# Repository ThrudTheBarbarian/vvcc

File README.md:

# vvcc
Variable-VCC circuit using an RP2040

This is a test-board to try out using a variable-pot controlled by an RP2040 to 
in turn control the voltage of a voltage regulator. That voltage will then be
provided to the other side of a level-shifter to insulate an FPGA from different
voltage inputs.

The level shifter in question can run at >400 MHz, which is the max toggle frequency of
the FPGA.

Simultaneously, I wanted to test out the USB component of the RP2040 and make sure I had
the design correct before laying down the FPGA board (which is a lot more expensive). the
RP2040 will be the last bastion against a bricked FPGA, so it'd be good to know that 
worked too.

So basically a testing-ground. Enjoy.

Thrud

# Update 25/May/2022

Boards came back today, with slightly mixed results. Plugging the first board in, the leds flickered, presumably magic smoke exited stage left, and the 3.3v power rail was churning out 1.1v...

Checking everything against the schematic, it seemed ok, nothing was placed the wrong way around, and even running through the boot process and (re)checking the default value for the I2C-controlled resistance looked like the resulting voltage from IC5 would be ok (4.3v by default).

I was left wondering whether the boot process did weird things with GPIOs, which seems vanishingly unlikely, but ... Anyway, holding down reset & boot buttons on a second board made that boot up ok, appear as RPI2_BOOT on the Mac, and none of the LEDs flashed, 3.3v rail seems ok (LED lights) etc. 

So my advice is that if you get these made, make sure you initialise it with known firmware before letting it boot on its own. 

Note: There is a pullup missing on the /CS line for the flash, but it's also missing in the RP2040 hardware design guide with the comment that they found they didn't need it. I'll definitely include it in future mind.

If booting it with working firmware still results in a problem, I'll update this. It's also possible the first board was just a dud... Once I have tested out the firmware thing, I might try sacrificing another board to see if it has the same behaviour as the first when booted up with no firmware in place.

Thrud

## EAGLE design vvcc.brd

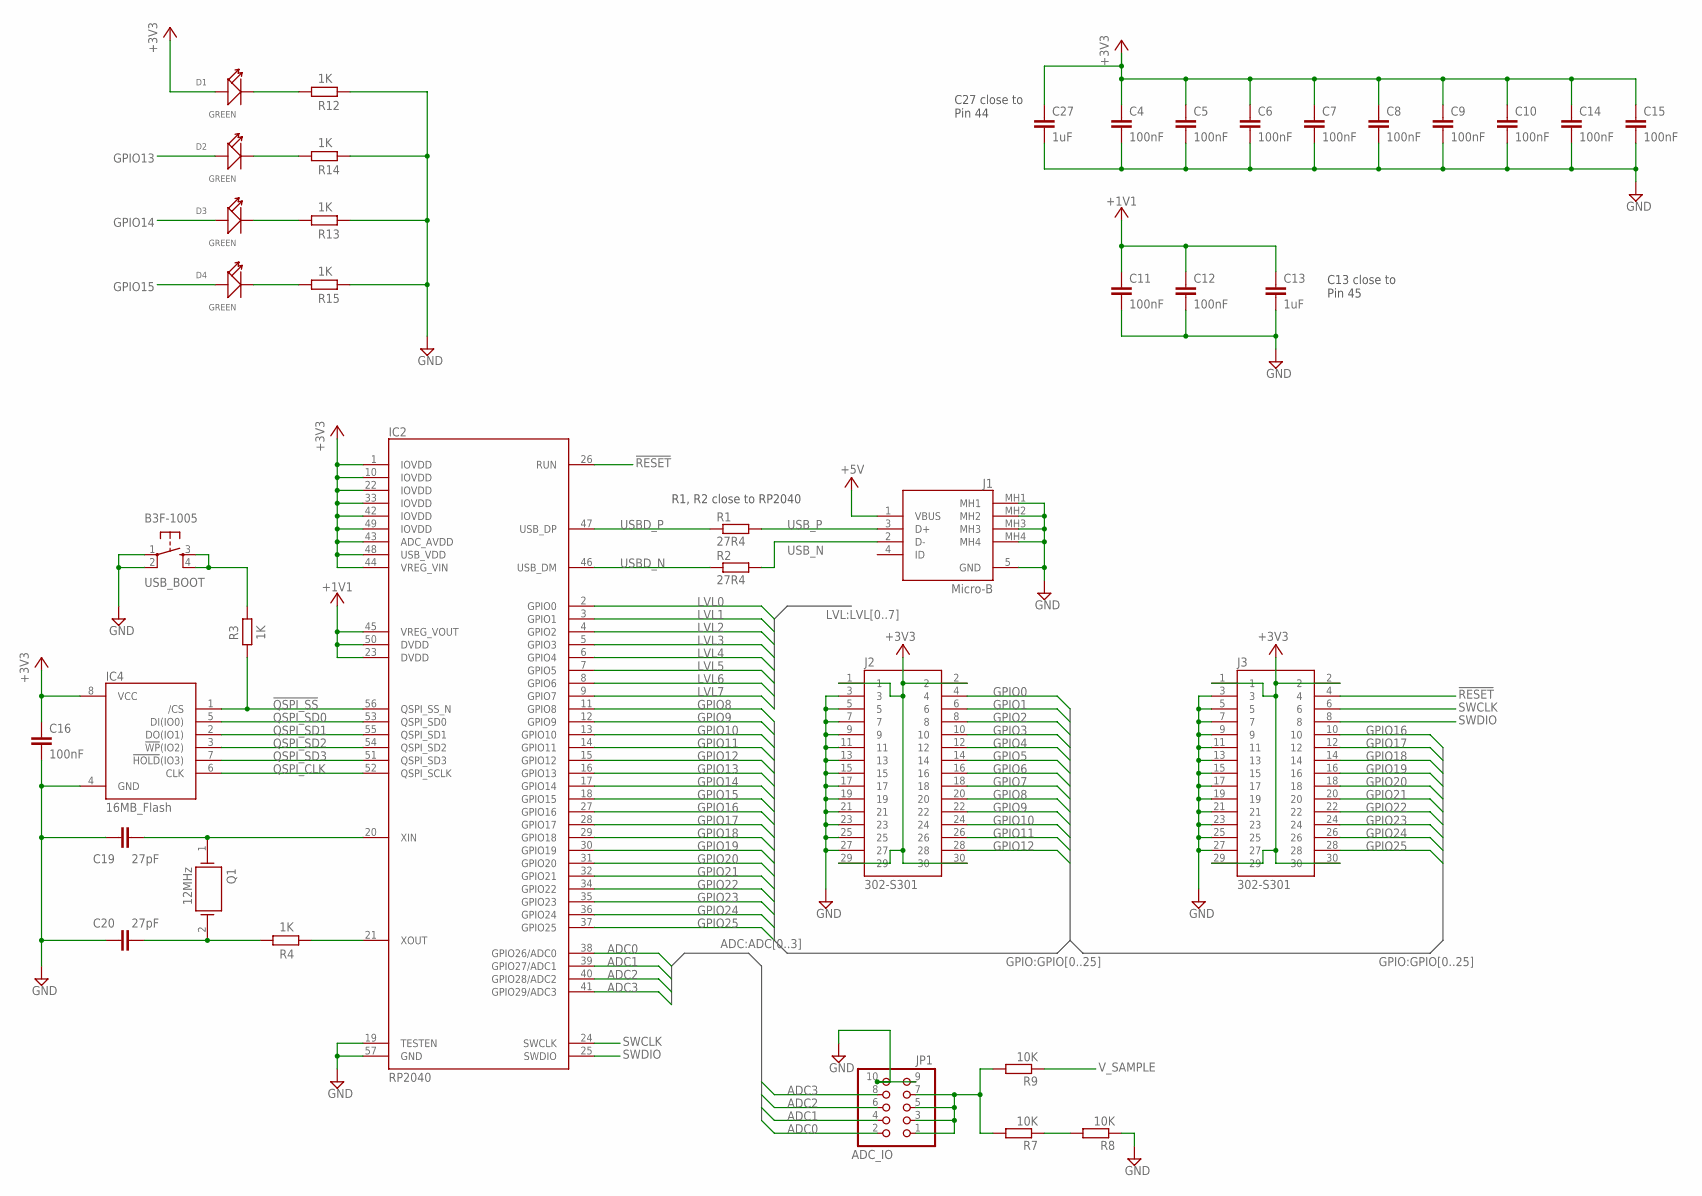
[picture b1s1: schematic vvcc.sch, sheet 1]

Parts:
C4, C5, C6, C7, C8, C9, C10, C11, C12, C14, C15, C16: 100nF; C0201
C13, C27: 1uF; C0201
C19, C20: 27pF; C0201
D1, D2, D3, D4: GREEN; LED-0603
IC2: RP2040; QFN40P700X700X90-57N
IC4: 16MB_Flash; SOIC127P790X216-8N
J1: Micro-B; MCRBSRASMTCS14TR
J2, J3: 302-S301; SHDR30W66P254_2X15_4572X910X91
JP1: ADC_IO; 2X05
Q1: 12MHz; HC/49US-(AT49)_1
R1, R2: 27R4; R0201
R3, R4, R12, R13, R14, R15: 1K; R0201
R7, R8, R9: 10K; R0201
USB_BOOT: B3F-1005; TACTILE-PTH

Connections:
!QSPI_SS!: IC2.56 (QSPI_SS_N), IC4.1 (/CS), R3.2
!RESET!: IC2.26 (RUN), J3.4; also elsewhere on the board
+1.8_FT: C11.1, C12.1, C13.1, IC2.23 (DVDD), IC2.45 (VREG_VOUT), IC2.50 (DVDD)
+3V3: C4.1, C5.1, C6.1, C7.1, C8.1, C9.1, C10.1, C14.1, C15.1, C16.1, C27.1, D1.+, IC2.1 (IOVDD), IC2.10 (IOVDD), IC2.22 (IOVDD), IC2.33 (IOVDD), IC2.42 (IOVDD), IC2.43 (ADC_AVDD), IC2.44 (VREG_VIN), IC2.48 (USB_VDD), IC2.49 (IOVDD), IC4.8 (VCC), J2.1, J2.2, J2.29, J2.30, J3.1, J3.2, J3.29, J3.30; also elsewhere on the board
+5V: J1.1 (VBUS); also elsewhere on the board
ADC0: IC2.38 (GPIO26/ADC0), JP1.2
ADC1: IC2.39 (GPIO27/ADC1), JP1.4
ADC2: IC2.40 (GPIO28/ADC2), JP1.6
ADC3: IC2.41 (GPIO29/ADC3), JP1.8
GND: C4.2, C5.2, C6.2, C7.2, C8.2, C9.2, C10.2, C11.2, C12.2, C13.2, C14.2, C15.2, C16.2, C19.2, C20.1, C27.2, IC2.19 (TESTEN), IC2.57 (GND), IC4.4 (GND), J1.5 (GND), J1.MH1, J1.MH2, J1.MH3, J1.MH4, J2.3, J2.5, J2.7, J2.9, J2.11, J2.13, J2.15, J2.17, J2.19, J2.21, J2.23, J2.25, J2.27, J3.3, J3.5, J3.7, J3.9, J3.11, J3.13, J3.15, J3.17, J3.19, J3.21, J3.23, J3.25, J3.27, JP1.9, JP1.10, R8.1, R12.2, R13.2, R14.2, R15.2, USB_BOOT.1, USB_BOOT.2; also elsewhere on the board
GPIO0: J2.4; also elsewhere on the board
GPIO1: J2.6; also elsewhere on the board
GPIO2: J2.8; also elsewhere on the board
GPIO3: J2.10; also elsewhere on the board
GPIO4: J2.12; also elsewhere on the board
GPIO5: J2.14; also elsewhere on the board
GPIO6: J2.16; also elsewhere on the board
GPIO7: J2.18; also elsewhere on the board
GPIO8: IC2.11 (GPIO8), J2.20; also elsewhere on the board
GPIO9: IC2.12 (GPIO9), J2.22; also elsewhere on the board
GPIO10: IC2.13 (GPIO10), J2.24
GPIO11: IC2.14 (GPIO11), J2.26
GPIO12: IC2.15 (GPIO12), J2.28; also elsewhere on the board
GPIO13: D2.+, IC2.16 (GPIO13); also elsewhere on the board
GPIO14: D3.+, IC2.17 (GPIO14)
GPIO15: D4.+, IC2.18 (GPIO15)
GPIO16: IC2.27 (GPIO16), J3.10
GPIO17: IC2.28 (GPIO17), J3.12
GPIO18: IC2.29 (GPIO18), J3.14
GPIO19: IC2.30 (GPIO19), J3.16
GPIO20: IC2.31 (GPIO20), J3.18
GPIO21: IC2.32 (GPIO21), J3.20
GPIO22: IC2.34 (GPIO22), J3.22
GPIO23: IC2.35 (GPIO23), J3.24
GPIO24: IC2.36 (GPIO24), J3.26
GPIO25: IC2.37 (GPIO25), J3.28
LVL0: IC2.2 (GPIO0); also elsewhere on the board
LVL1: IC2.3 (GPIO1); also elsewhere on the board
LVL2: IC2.4 (GPIO2); also elsewhere on the board
LVL3: IC2.5 (GPIO3); also elsewhere on the board
LVL4: IC2.6 (GPIO4); also elsewhere on the board
LVL5: IC2.7 (GPIO5); also elsewhere on the board
LVL6: IC2.8 (GPIO6); also elsewhere on the board
LVL7: IC2.9 (GPIO7); also elsewhere on the board
unnamed: C19.1, IC2.20 (XIN), Q1.1
unnamed: C20.2, Q1.2, R4.1
unnamed: D1.-, R12.1
unnamed: D2.-, R14.1
unnamed: R3.1, USB_BOOT.3, USB_BOOT.4
unnamed: D3.-, R13.1
unnamed: IC2.21 (XOUT), R4.2
unnamed: D4.-, R15.1
unnamed: JP1.1, JP1.3, JP1.5, JP1.7, R7.2, R9.2
unnamed: R7.1, R8.2
QSPI_CLK: IC2.52 (QSPI_SCLK), IC4.6 (CLK)
QSPI_SD0: IC2.53 (QSPI_SD0), IC4.5 (DI(IO0))
QSPI_SD1: IC2.55 (QSPI_SD1), IC4.2 (DO(IO1))
QSPI_SD2: IC2.54 (QSPI_SD2), IC4.3 (!WP!(IO2))
QSPI_SD3: IC2.51 (QSPI_SD3), IC4.7 (!HOLD!(IO3))
SWCLK: IC2.24 (SWCLK), J3.6
SWDIO: IC2.25 (SWDIO), J3.8
USBD_N: IC2.46 (USB_DM), R2.1
USBD_P: IC2.47 (USB_DP), R1.1
USB_N: J1.2 (D-), R2.2
USB_P: J1.3 (D+), R1.2
V_SAMPLE: R9.1; also elsewhere on the board

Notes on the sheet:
R1, R2 close to RP2040
C13 close to Pin 45
C27 close to Pin 44

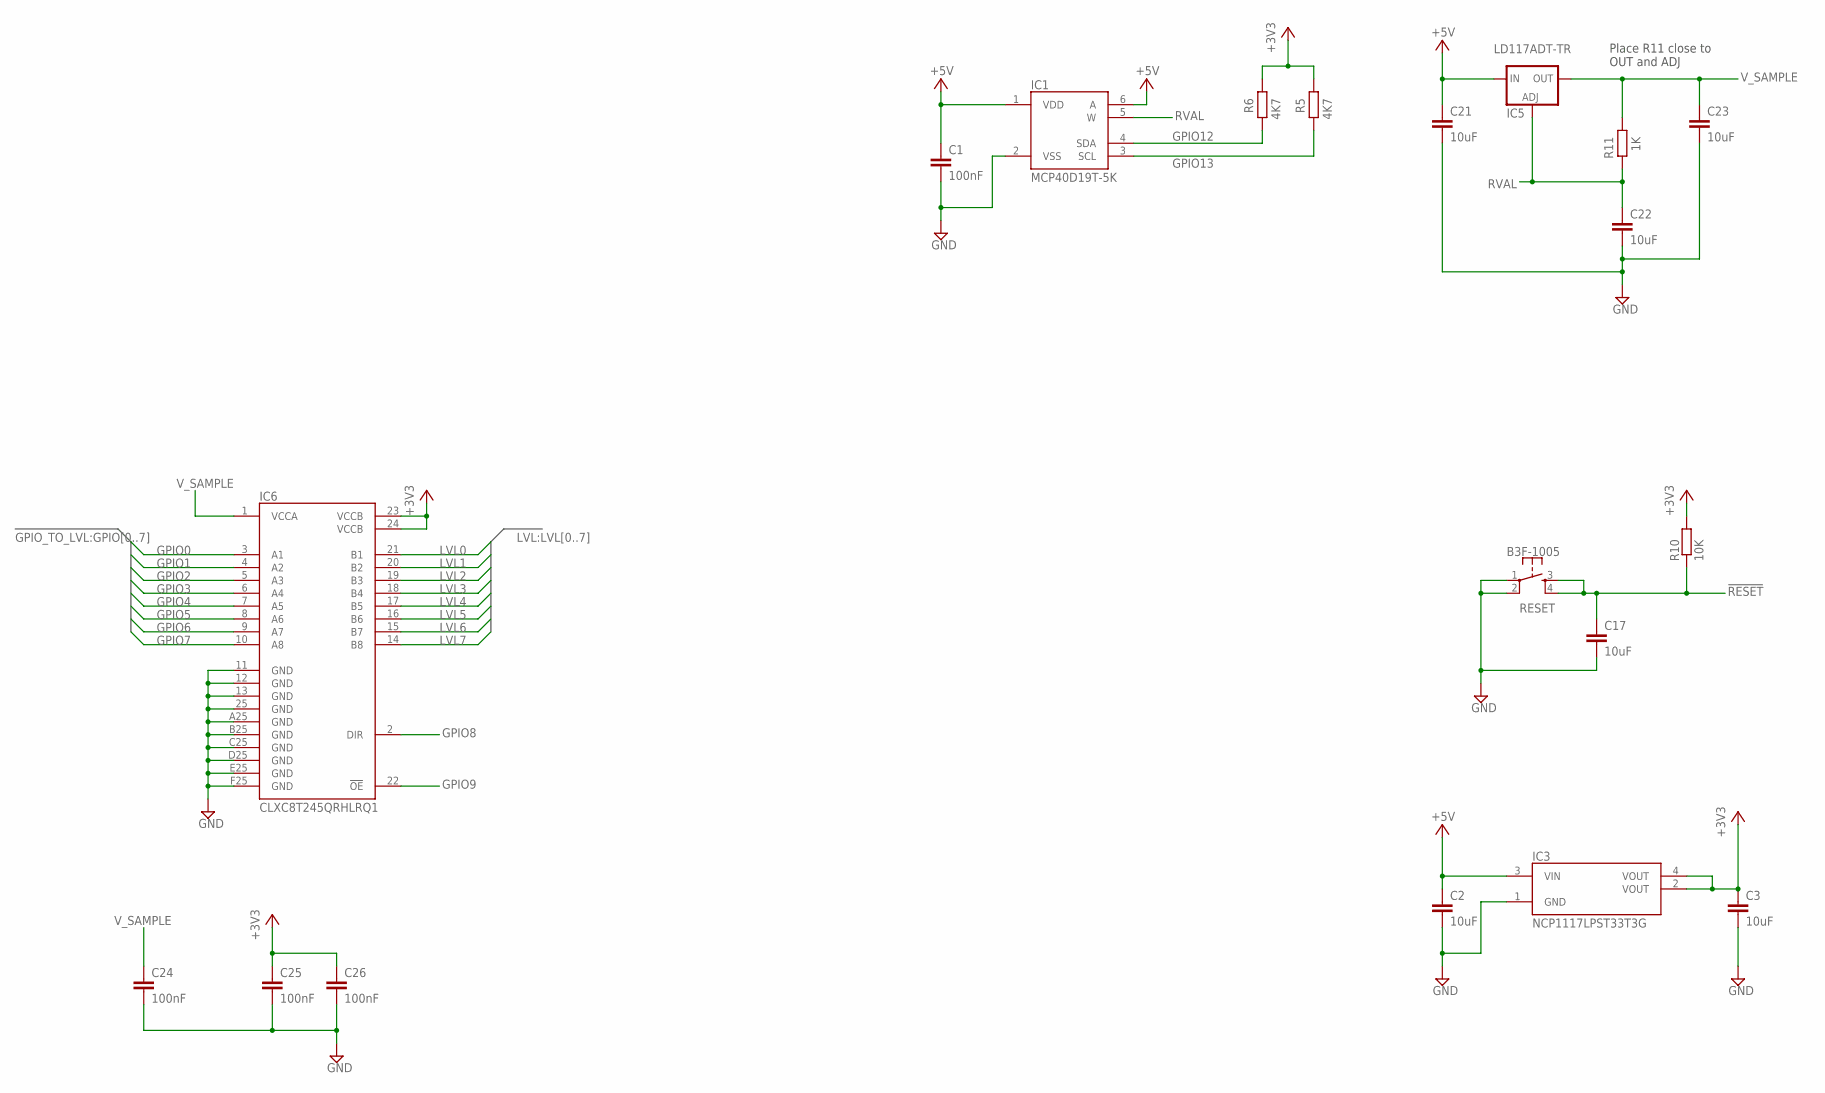
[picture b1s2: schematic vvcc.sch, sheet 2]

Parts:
C1, C24, C25, C26: 100nF; C0201
C2, C3, C17, C21, C22, C23: 10uF; C0402
IC1: MCP40D19T-5K; SOP65P210X110-6N
IC3: NCP1117LPST33T3G; SOT230P700X180-4N
IC5: LD117ADT-TR; DPACK
IC6: CLXC8T245QRHLRQ1
R5, R6: 4K7; R0201
R10: 10K; R0201
R11: 1K; R0201
RESET: B3F-1005; TACTILE-PTH

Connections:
!RESET!: C17.1, R10.1, RESET.3, RESET.4; also elsewhere on the board
+3V3: C3.1, C25.1, C26.1, IC3.2 (VOUT), IC3.4 (VOUT), IC6.23 (VCCB), IC6.24 (VCCB), R5.1, R6.1, R10.2; also elsewhere on the board
+5V: C1.1, C2.1, C21.1, IC1.1 (VDD), IC1.6 (A), IC3.3 (VIN), IC5.3 (IN); also elsewhere on the board
GND: C1.2, C2.2, C3.2, C17.2, C21.2, C22.2, C23.2, C24.2, C25.2, C26.2, IC1.2 (VSS), IC3.1 (GND), IC6.11 (GND), IC6.12 (GND), IC6.13 (GND), IC6.25 (GND), IC6.A25 (GND), IC6.B25 (GND), IC6.C25 (GND), IC6.D25 (GND), IC6.E25 (GND), IC6.F25 (GND), RESET.1, RESET.2; also elsewhere on the board
GPIO0: IC6.3 (A1); also elsewhere on the board
GPIO1: IC6.4 (A2); also elsewhere on the board
GPIO2: IC6.5 (A3); also elsewhere on the board
GPIO3: IC6.6 (A4); also elsewhere on the board
GPIO4: IC6.7 (A5); also elsewhere on the board
GPIO5: IC6.8 (A6); also elsewhere on the board
GPIO6: IC6.9 (A7); also elsewhere on the board
GPIO7: IC6.10 (A8); also elsewhere on the board
GPIO8: IC6.2 (DIR); also elsewhere on the board
GPIO9: IC6.22 (!OE); also elsewhere on the board
GPIO12: IC1.4 (SDA), R6.2; also elsewhere on the board
GPIO13: IC1.3 (SCL), R5.2; also elsewhere on the board
LVL0: IC6.21 (B1); also elsewhere on the board
LVL1: IC6.20 (B2); also elsewhere on the board
LVL2: IC6.19 (B3); also elsewhere on the board
LVL3: IC6.18 (B4); also elsewhere on the board
LVL4: IC6.17 (B5); also elsewhere on the board
LVL5: IC6.16 (B6); also elsewhere on the board
LVL6: IC6.15 (B7); also elsewhere on the board
LVL7: IC6.14 (B8); also elsewhere on the board
RVAL: C22.1, IC1.5 (W), IC5.1 (ADJ), R11.2
V_SAMPLE: C23.1, C24.1, IC5.4 (OUT), IC6.1 (VCCA), R11.1; also elsewhere on the board

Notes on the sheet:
Place R11 close to OUT and ADJ

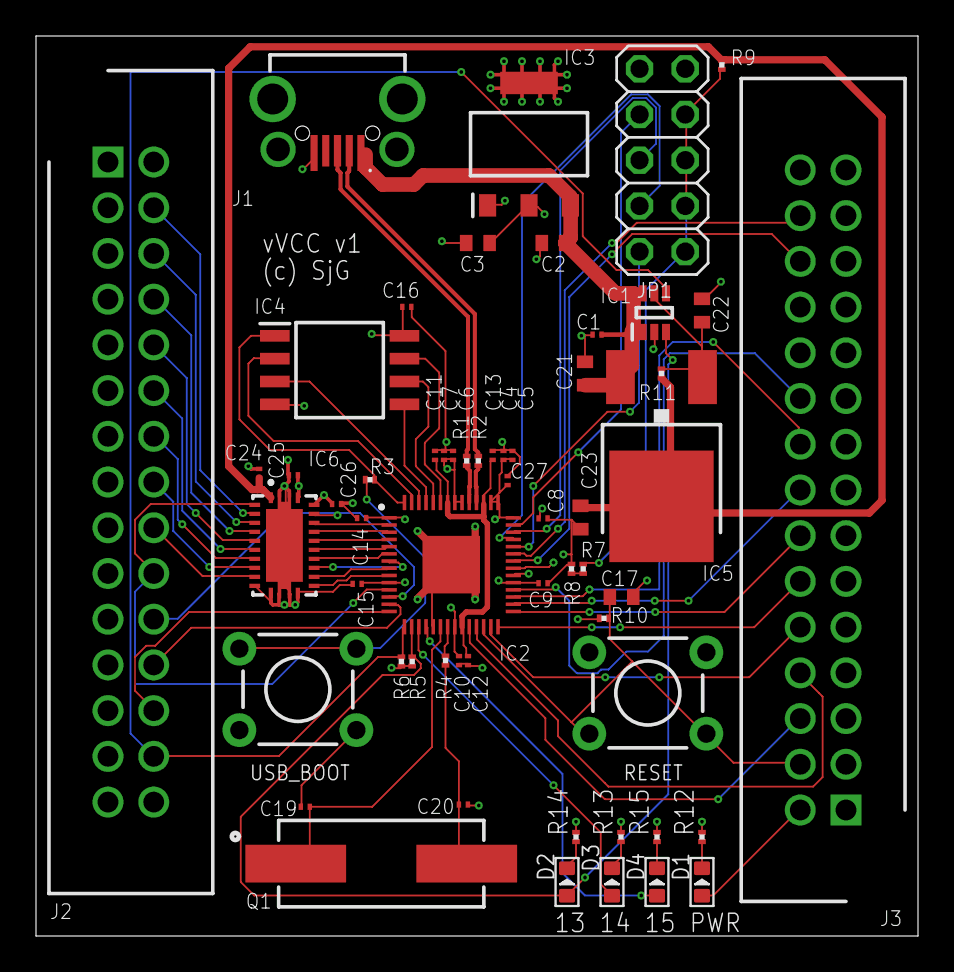
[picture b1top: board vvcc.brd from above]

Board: 4 copper layers, 49.0 x 50.0 mm, 58 parts (0 on the bottom side), 67 nets.

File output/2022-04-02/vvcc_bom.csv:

"Qty";"Value";"Device";"Package";"Parts";"Description";"ARROW_PART_NUMBER";"ARROW_PRICE-STOCK";"DESCRIPTION";"HEIGHT";"MANUFACTURER_NAME";"MANUFACTURER_PART_NUMBER";"MOUSER_PART_NUMBER";"MOUSER_PRICE-STOCK";"POPULARITY";"SPICEPREFIX";"USE";
"17";"100nF";"C-EUC0201";"C0201";"C1, C4, C5, C6, C7, C8, C9, C10, C11, C12, C14, C15, C16, C18, C24, C25, C26";"CAPACITOR, European symbol";"";"";"";"";"";"";"";"";"0";"C";"0201X104M160CT";
"4";"10K";"R-EU_R0201";"R0201";"R7, R8, R9, R10";"RESISTOR, European symbol";"";"";"";"";"";"";"";"";"0";"R";"CR0201-JW-103GLF";
"6";"10uF";"C-EUC0402";"C0402";"C2, C3, C17, C21, C22, C23";"CAPACITOR, European symbol";"";"";"";"";"";"";"";"";"18";"C";"GRM155R60J106ME15D";
"1";"12MHz";"ABLS-12.000MHZ-B4-T";"HC/49US-(AT49)_1";"Q1";"ABRACON - ABLS-12.000MHZ-B4-T - CRYSTAL, 12MHZ, 18PF, HC-49US";"ABLS-12.000MHZ-B4-T";"https://www.arrow.com/en/products/abls-12.000mhz-b4-t/abraco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";"ABRACON - ABLS-12.000MHZ-B4-T - CRYSTAL, 12MHZ, 18PF, HC-49US";"mm";"ABRACON";"ABLS-12.000MHZ-B4-T";"815-ABLS-12.0M-T";"https://www.mouser.co.uk/ProductDetail/ABRACON/ABLS-12000MHZ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";"";"";"ABLS-12.000MHZ-B4-T";
"1";"16MB_Flash";"W25Q128JVSIM_TR";"SOIC127P790X216-8N";"IC4";"3V 128M-BIT SERIAL FLASH MEMORY WITH DUAL/QUAD SPI & QPI & DTR";"W25Q128JVSIM TR";"https://www.arrow.com/en/products/w25q128jvsimtr/winbond-ele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";"3V 128M-BIT SERIAL FLASH MEMORY WITH DUAL/QUAD SPI & QPI & DTR";"2.16mm";"Winbond";"W25Q128JVSIM TR";"454-W25Q128JVSIMTR";"https://www.mouser.co.uk/ProductDetail/Winbond/W25Q128JVSIM-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";"";"";"W25Q128JVSIM";
"3";"1K";"R-EU_R0201";"R0201";"R3, R4, R11";"RESISTOR, European symbol";"";"";"";"";"";"";"";"";"0";"R";"RC0201FR-071KL";
"2";"1uF";"C-EUC0201";"C0201";"C13, C27";"CAPACITOR, European symbol";"";"";"";"";"";"";"";"";"0";"C";"0201B102K250CT";
"2";"27R4";"R-EU_R0201";"R0201";"R1, R2";"RESISTOR, European symbol";"";"";"";"";"";"";"";"";"0";"R";"RC0201FR-0727R4L";
"2";"27pF";"C-EUC0201";"C0201";"C19, C20";"CAPACITOR, European symbol";"";"";"";"";"";"";"";"";"0";"C";"C0201C270J3GAC7867";
"2";"302-S301";"302-S301";"SHDR30W66P254_2X15_4572X910X91";"J2, J3";"Dual row vertical box header";"302-S301";"https://www.arrow.com/en/products/302-s301/on-shore-technology";"Dual row vertical box header";"9.1mm";"On-Shore Technology, Inc";"302-S301";"";"";"";"";"302-S301";
"2";"4K7";"R-EU_R0201";"R0201";"R5, R6";"RESISTOR, European symbol";"";"";"";"";"";"";"";"";"0";"R";"ERJ-1GNJ472C";
"1";"ADC_IO";"PINHD-2X5";"2X05";"JP1";"PIN HEADER";"";"";"";"";"";"";"";"";"35";"";"TSHS-105-D-06-A-T-LF";
"2";"B3F-1005";"TAC_SWITCHPTH";"TACTILE-PTH";"RESET, USB_BOOT";"Momentary Switch";"";"";"";"";"";"";"";"";"";"";"B3F-1005";
"1";"CLXC8T245QRHLRQ1";"CLXC8T245QRHLRQ1";"CLXC8T245QRHLRQ1";"IC6";"Translation - Voltage Levels Automotive 8-bit dual-supply wide voltage level translating transceiver with tri-state output";"CLXC8T245QRHLRQ1";"https://www.arrow.com/en/products/clxc8t245qrhlrq1/texas-ins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";"Translation - Voltage Levels Automotive 8-bit dual-supply wide voltage level translating transceiver with tri-state output";"1mm";"Texas Instruments";"CLXC8T245QRHLRQ1";"595-CLXC8T245QRHLRQ1";"https://www.mouser.co.uk/ProductDetail/Texas-Instruments/CLX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";"";"";"CLXC8T245QRHLRQ1";
"1";"LD117ADT-TR";"LD117ADT-TR";"DPACK";"IC5";"Low drop fixed and adjustable positive voltage regulators 1 A";"";"";"";"";"";"";"";"";"0";"";"LD1117ADT-TR";
"1";"MCP40D19T-5K";"MCP40D18T-104E_LT";"SOP65P210X110-6N";"IC1";"MCP40D18T-104E/LT, Digital Potentiometer 100k 128-Position Linear Serial-I2C 6-Pin SC-70";"MCP40D18T-104E/LT";"https://www.arrow.com/en/products/mcp40d18t-104elt/microchip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";"MCP40D18T-104E/LT, Digital Potentiometer 100k 128-Position Linear Serial-I2C 6-Pin SC-70";"1.1mm";"Microchip";"MCP40D18T-104E/LT";"579-MCP40D18T104E/LT";"https://www.mouser.co.uk/ProductDetail/Microchip-Technology/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";"";"";"MCP4019T-502E/LT";
"1";"MIC803-30D3VM3-TR";"MIC803-30D2VM3-TR";"SOT95P237X111-3N";"SPV";"Supervisory Circuits 3-Pin Microprocessor Supervisor Circuit w/ Open-Drain Reset Output";"MIC803-30D2VM3-TR";"https://www.arrow.com/en/products/mic803-30d2vm3-tr/microchi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";"Supervisory Circuits 3-Pin Microprocessor Supervisor Circuit w/ Open-Drain Reset Output";"1.11mm";"Microchip";"MIC803-30D2VM3-TR";"998-MIC803-30D2VM3TR";"https://www.mouser.co.uk/ProductDetail/Microchip-Technology-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";"";"";"MIC803-30D3VM3-TR";
"1";"Micro-B";"MCR-B-S-RA-SMT-CS14-T_R";"MCRBSRASMTCS14TR";"J1";"USB - micro B Receptacle Connector 5 Position Surface Mount, Right Angle";"MCR-B-S-RA-SMT-CS14-T/R";"https://www.arrow.com/en/products/mcr-b-s-ra-smt-cs14-tr/ada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";"USB - micro B Receptacle Connector 5 Position Surface Mount, Right Angle";"3.1mm";"Adam Tech";"MCR-B-S-RA-SMT-CS14-T/R";"";"";"";"";"MCR-B-S-RA-SMT-CS14-T_R";
"1";"NCP1117LPST33T3G";"NCP1117LPST33T3G";"SOT230P700X180-4N";"IC3";"ON SEMICONDUCTOR - NCP1117LPST33T3G - Fixed LDO Voltage Regulator, 18V in, 1.3V Dropout, 3.3V/1A out, SOT-223-3";"NCP1117LPST33T3G";"https://www.arrow.com/en/products/ncp1117lpst33t3g/on-semico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";"ON SEMICONDUCTOR - NCP1117LPST33T3G - Fixed LDO Voltage Regulator, 18V in, 1.3V Dropout, 3.3V/1A out, SOT-223-3";"1.8mm";"ON Semiconductor";"NCP1117LPST33T3G";"863-NCP1117LPST33T3G";"https://www.mouser.co.uk/ProductDetail/onsemi/NCP1117LPST33T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";"";"";"NCP1117LPST33T3G";
"1";"RP2040";"RP2040";"QFN40P700X700X90-57N";"IC2";"Microcontroller in QFN Package";"";"";"Microcontroller in QFN Package";"0.9mm";"RASPBERRY-PI";"RP2040";"";"";"";"";"SC0914(13)";

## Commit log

2022-04-02 Initial import
2022-04-02 Change the layout a little to group +5v closer together
2022-04-02 Add in a missing 0.1uF capacitor on +3v3
2022-04-02 Fix a few errors in the schematic. It is good to connect GND to the chip...
2022-04-02 Make sure everything has a USE attribute
2022-04-02 Submit for creation
2022-04-03 Better board layout - and added LEDs. This was the real submit to nextpcb
2022-05-24 Boards came back
2022-05-24 Fix README, hopefully
2022-05-24 Clarification
2022-05-24 I should save text before doing git push...

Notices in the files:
parts and their libraries:
SparkFun: Licensing: CC v3.0 Share-Alike You are welcome to use this library for commercial purposes.
